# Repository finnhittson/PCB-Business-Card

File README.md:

# PCB Business Card

This repo contains all information needed to make a PCB business card. The card features NFC IC that allows users to tap their phone and receive the stored data on the card. Ideally this card is used at recruiting events to share a resume or a portfolio while also demonstrating one’s ability to make such a card. It also doubles as a fun way to rick roll your friends. This repo has a template for users to make their own PCB business card using the KiCad files in the `electrical/` directory and the necessary software to configure the NFC tag in the `software/` directory. The image below is my personal business card, but this repo also contains steps I took to make these cards in bulk. To see a demonstration of these cards working see this [link](https://youtu.be/k8sX_htg_Z4) and to see different designs see this [link](https://youtu.be/7vKhVwrzvhk).

## Electrical

The schematic for the business card is very simple consisting of 5 devices. There is a resistor and LED to add effect and ambiance to the PCB and show the result of effective energy harvesting. There is a capacitor to store energy from the coil antenna. And finally, there is the NFC IC which is responsible for harvesting the energy captured by the coil, storing the data in EEPROM, and communicating with the phone. The following is the schematic for the card drawn in KiCad.

The IC used for this is the [NT3H2111W0FHKH](https://www.digikey.com/en/products/detail/nxp-usa-inc/NT3H2111W0FHKH/5872977?s=N4IgTCBcDaIKwDYAcBaAjGAnABmysKAcgCIgC6AvkA). The most engineeringly complex part of this card is the design of the antenna. The antenna effectively is an inductor that captures the magnetic field radiated from the phone. The phone generates an oscillating magnetic field at 13.56MHz and the capacitor on the IC forms a resonant take with the inductor to maximize energy captured. Thus, to design the antenna you can use the LC resonance formula below to calculate the value of inductance required. The datasheets recommends using a 220pF capacitor and with the frequency set to 13.56MHz we can rearrange and calculate the value for L.

$f_0=\frac{1}{2\pi\sqrt{LC}}$

Going through the math it is roughly 626nH. Next is to design the physical shape of the antenna and make sure it has 626nH of inductance. There are many inductor calculators online, but I found [this](https://eds.st.com/antenna/#/) one to be most helpful. This calculator lets you give dimensions for your antenna which is very helpful since we want this on a PCB with credit card dimensions. The next thing is to make a footprint with the same dimensions that the antenna calculator created. The image below is an image of the antenna laid out on a PCB template.

With the PCB you can then modify the front and back silkscreen to have your name, phone number, and title. The backside can then have an image in which you can integrate an LED to add a cool effect.

## Software

Annoyingly the [NT3H2111W0FHKH](https://www.digikey.com/en/products/detail/nxp-usa-inc/NT3H2111W0FHKH/5872977?s=N4IgTCBcDaIKwDYAcBaAjGAnABmysKAcgCIgC6AvkA) IC come off the fab line in a read only state. I learned this the hard way when I soldered all my devices to my PCB card and couldn't write to it. To fix this I made another PCB to act as my programmer board that would unlock the ICs and then I would solder these unlocked ICs to the business cards. I wanted to use the smallest IC's possible, so the package type is an 8 pin QFN style package which is mighty small. I hot air gunned the IC to the PCB then programmed it using an Arduino as shown in the image below.

What the Arduino code is setting is the capability container (CC), described on page 25 of the datasheet, to have read and write access. This is done by setting the registers outlined in Table 8. This gives the CC register read write access.

However, because of the way memory is organized in this IC, caution needs to be taken so that you do not change other settings. When reading and writing to these registers you can only read and write to an entire page which contains more information than you need. A page at 16 bytes and we only need to modify 4 at a time. Therefore, the software reads a page, modifies the 4 bytes while leaving the other 12 unchanged, and then writes the entire page back to memory. Another caveat is that in enabling read write access for CC, the I2C address changes from 0x55 to 0x02 and you need to repeat the process twice; once for the 0x55 address and once for the 0x02 address. I found it easiest to start with the 0x55 address, verify the device was visible on the I2C bus, write my data, and repeat the process. I knew the write was successful if when I checked the I2C bus again I would see a device at 0x02 and no other address.

Once all of this was done and the unlocked IC is soldered to the board, I used NFC Tools app to program the IC to either my resume, linked account, or this [link](https://www.youtube.com/watch?v=dQw4w9WgXcQ).

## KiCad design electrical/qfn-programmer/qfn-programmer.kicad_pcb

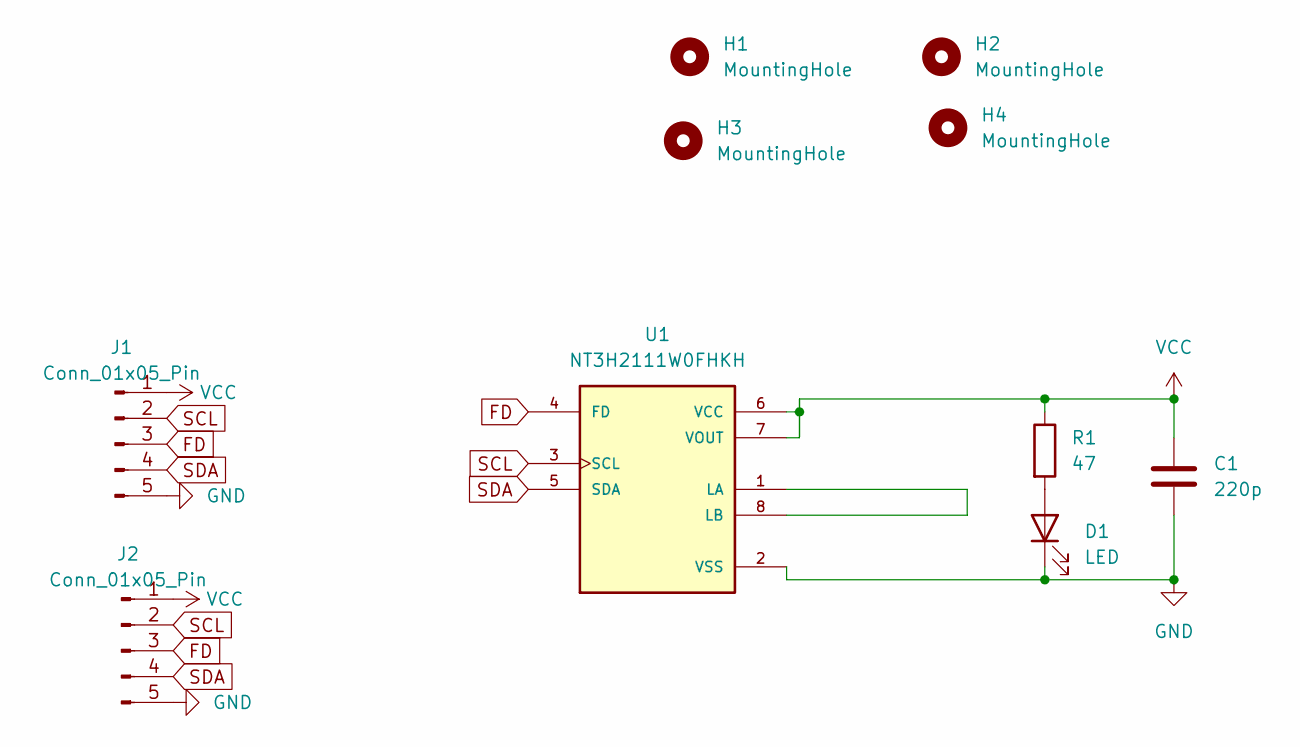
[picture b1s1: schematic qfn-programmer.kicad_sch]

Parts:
C1: 220p; C_0805_2012Metric
D1: LED; LED_0805_2012Metric
H1, H2, H3, H4: MountingHole; MountingHole_3.2mm_M3_DIN965_Pad_TopBottom
J1, J2: Conn_01x05_Pin; PinSocket_1x05_P2.54mm_Vertical
R1: 47; R_0805_2012Metric
U1: NT3H2111W0FHKH; QFN8P50_160X160X50L40X20N

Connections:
FD: J1.3, J2.3, U1.4 (FD)
GND: C1.2, D1.1 (K), J1.5, J2.5, U1.2 (VSS)
unnamed: D1.2 (A), R1.2
unnamed: U1.1 (LA), U1.8 (LB)
SCL: J1.2, J2.2, U1.3 (SCL)
SDA: J1.4, J2.4, U1.5 (SDA)
VCC: C1.1, J1.1, J2.1, R1.1, U1.6 (VCC), U1.7 (VOUT)

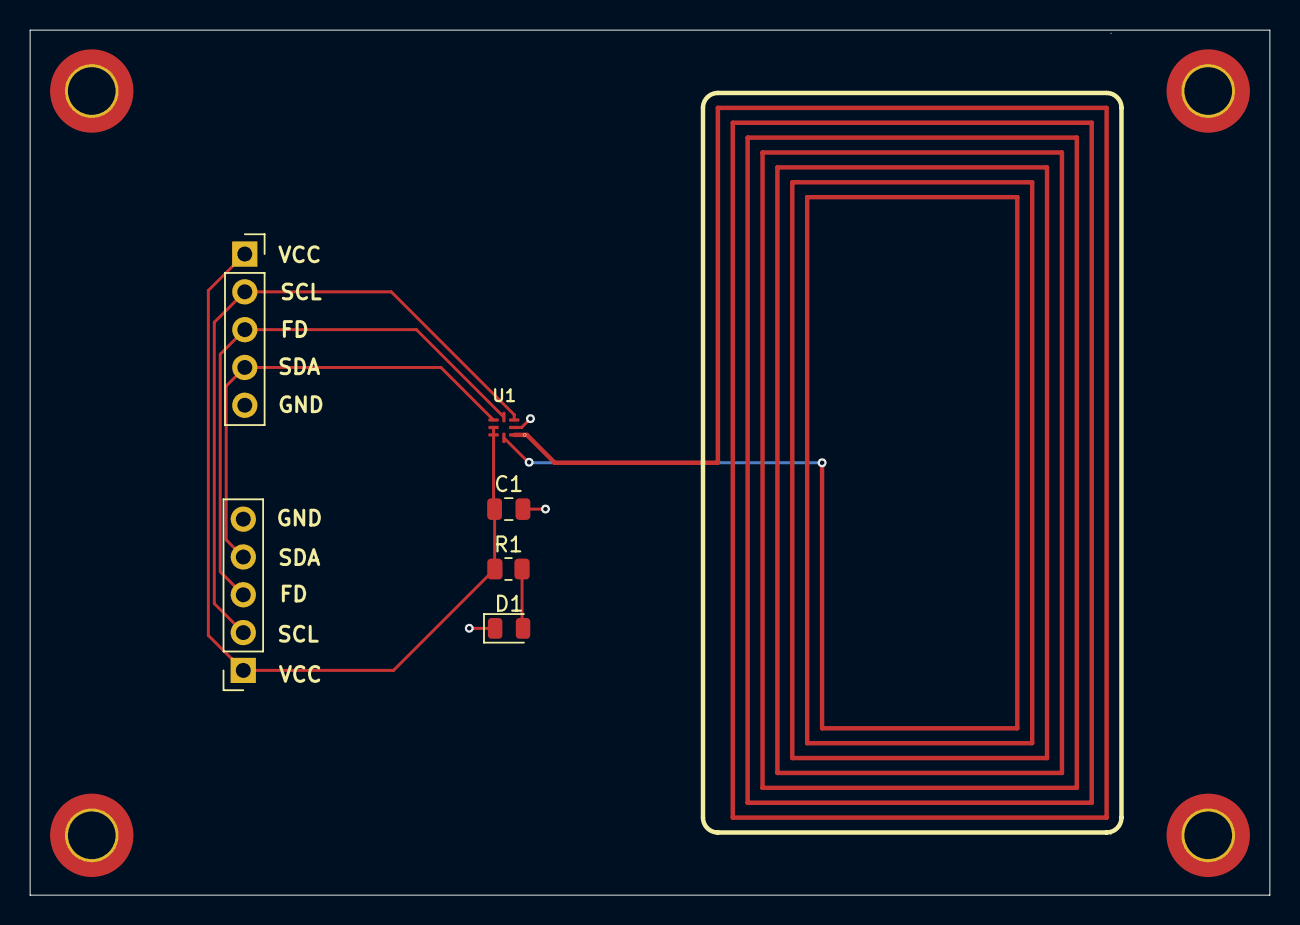
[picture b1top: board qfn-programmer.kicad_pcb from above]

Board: 2 copper layers, 83.3 x 58.1 mm, 10 parts (0 on the bottom side), 7 nets.

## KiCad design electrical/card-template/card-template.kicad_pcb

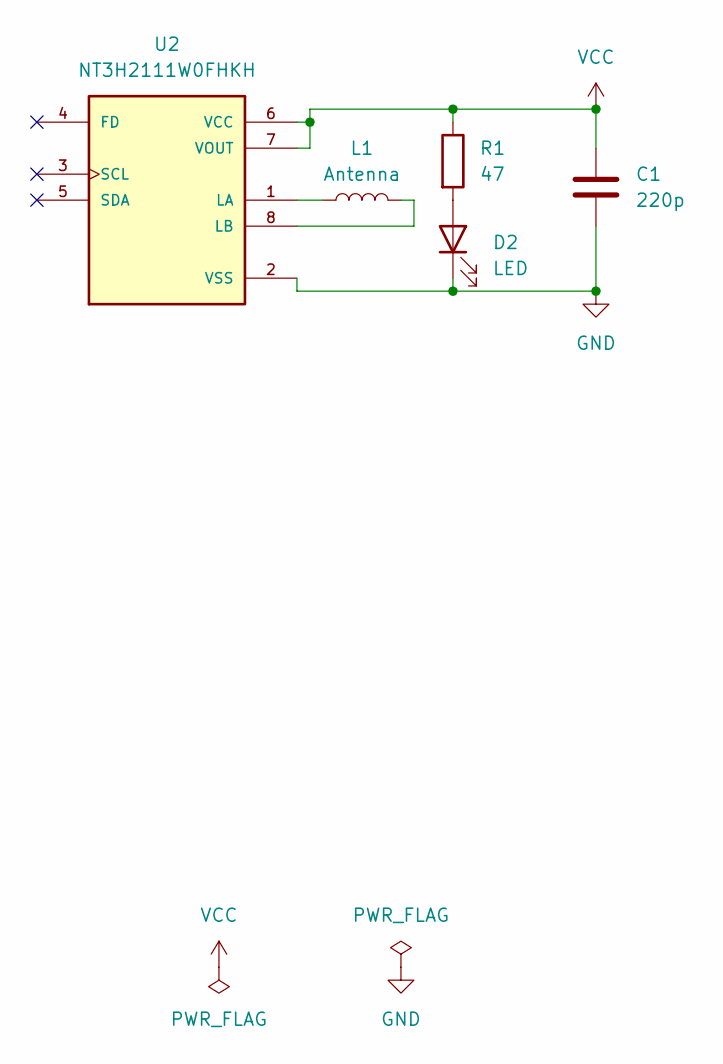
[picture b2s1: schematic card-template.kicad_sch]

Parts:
C1: 220p; C_0402_1005Metric
D2: LED; LED_0402_1005Metric
L1: Antenna
R1: 47; R_0402_1005Metric
U2: NT3H2111W0FHKH; QFN8P50_160X160X50L40X20N

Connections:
GND: C1.2, D2.1 (K), U2.2 (VSS)
unnamed: D2.2 (A), R1.2
unnamed: L1.1, U2.1 (LA)
unnamed: L1.2, U2.8 (LB)
VCC: C1.1, R1.1, U2.6 (VCC), U2.7 (VOUT)

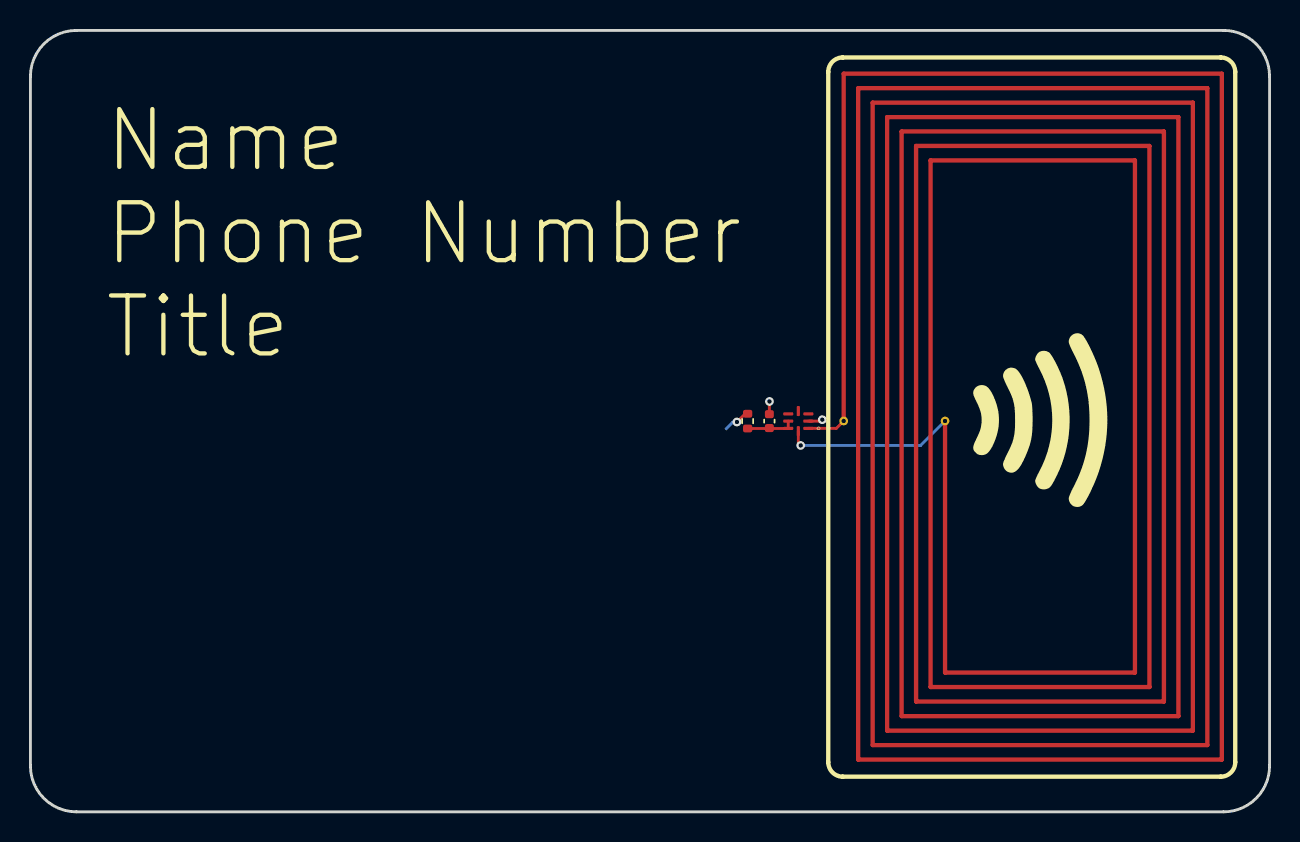
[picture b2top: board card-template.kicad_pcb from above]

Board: 2 copper layers, 85.6 x 54.0 mm, 5 parts (1 on the bottom side), 5 nets.
